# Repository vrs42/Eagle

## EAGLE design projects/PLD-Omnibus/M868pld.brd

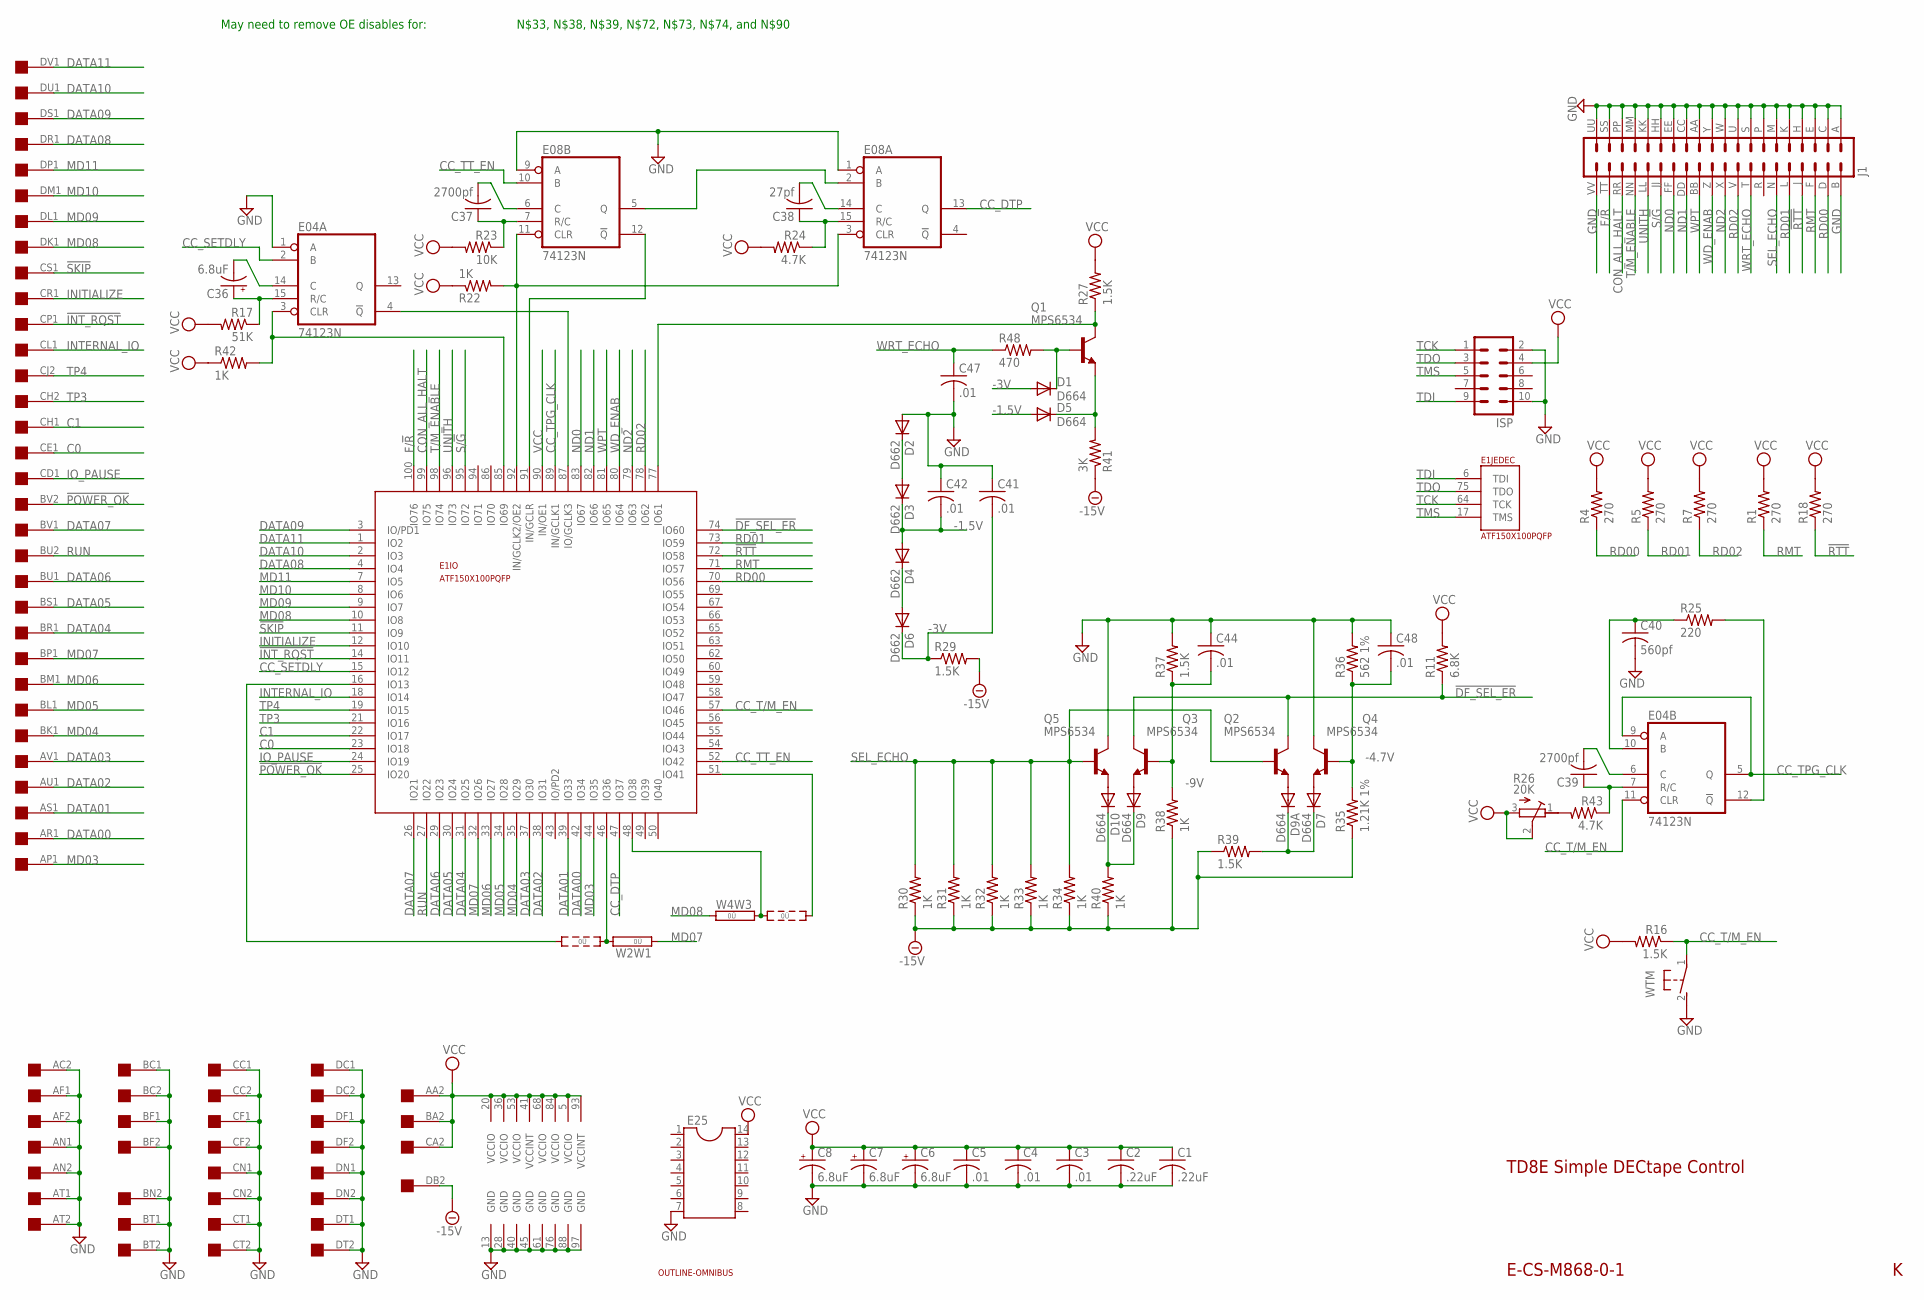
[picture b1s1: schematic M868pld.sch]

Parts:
C1, C2: .22uF; C050-025X075
C3, C4, C5, C41, C42, C44, C47, C48: .01; C050-025X075
C6, C7, C8, C36: 6.8uF; E12-8
C37, C39: 2700pf; C102-043X133
C38: 27pf; C050-025X075
C40: 560pf; C075-032X103
D1, D5, D7, D9, D9A, D10: D664; DO35-10
D2, D3, D4, D6: D662; DO35-10
E1: ATF150X100PQFP; PQFP-100
E04, E08: 74123N; DIL16
E25: DIL14
EDGE$3: QUAD; EDGE-CON8
ISP: MA05-2
J1: DEC40PINH
Q1, Q2, Q3, Q4, Q5: MPS6534; TO5
R1, R4, R5, R7, R18: 270; 0207/10
R11: 6.8K; 0207/10
R16, R27, R29, R37, R39: 1.5K; 0207/10
R17: 51K; 0207/10
R22, R30, R31, R32, R33, R34, R38, R40, R42: 1K; 0207/10
R23: 10K; 0207/10
R24, R43: 4.7K; 0207/10
R25: 220; 0207/10
R26: 20K; 3006Y
R35: 1.21K 1%; 0207/15
R36: 562 1%; 0207/15
R41: 3K; 0207/10
R48: 470; 0207/10
U$1: OUTLINE-OMNIBUS; OMNIBUS
W2W1, W4W3: 0R2; 0R2/10
WTM: 31-XX; B3F-31XX

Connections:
!CC_TPG_CLK: C40.1, E04.10 (B), R25.1
!DF_SEL_ER: E1.74 (IO60), Q2.3 (C), Q3.3 (C), R11.1
!INT_RQST: E1.14 (IO11), EDGE$3.CP1
!POWER_OK: E1.25 (IO20), EDGE$3.BV2
!RTT: E1.72 (IO58), J1.J (8), R18.1
!SKIP: E1.11 (IO9), EDGE$3.CS1
-1.5V: C42.2, D3.C, D4.A, D5.A
-3V: C41.2, D1.A, D6.C, R29.1
-4.7V: C48.2, Q4.2 (B), R35.2, R36.1
-9V: C44.2, Q3.2 (B), R37.1, R38.2
-15V: EDGE$3.DB2, R29.2, R30.1, R31.1, R32.1, R33.1, R34.1, R35.1, R38.1, R39.1, R40.1, R41.1
C0: E1.23 (IO18), EDGE$3.CE1
C1: E1.22 (IO17), EDGE$3.CH1
CC_DTP: E1.47 (IO37), E08.13 (Q)
CC_SETDLY: E1.15 (IO12), E04.2 (B)
CC_T/M_EN: E1.57 (IO46), E04.11 (CLR), R16.1, WTM.1
CC_TPG_CLK: E1.89 (IN/GCLK1), E04.5 (Q), E04.9 (A)
CC_TT_EN: E1.52 (IO42), E08.10 (B)
CON_ALL_HALT: E1.99 (IO75), J1.RR (36)
DATA00: E1.42 (IO34), EDGE$3.AR1
DATA01: E1.39 (IO33), EDGE$3.AS1
DATA02: E1.38 (IO31), EDGE$3.AU1
DATA03: E1.37 (IO30), EDGE$3.AV1
DATA04: E1.31 (IO25), EDGE$3.BR1
DATA05: E1.30 (IO24), EDGE$3.BS1
DATA06: E1.29 (IO23), EDGE$3.BU1
DATA07: E1.26 (IO21), EDGE$3.BV1
DATA08: E1.4 (IO4), EDGE$3.DR1
DATA09: E1.3 (IO/PD1), EDGE$3.DS1
DATA10: E1.2 (IO3), EDGE$3.DU1
DATA11: E1.1 (IO2), EDGE$3.DV1
F/!R: E1.100 (IO76), J1.TT (38)
GND: C1.2, C2.2, C3.2, C4.2, C5.2, C6.-, C7.-, C8.-, C40.2, C41.1, C42.1, C44.1, C47.2, C48.1, D2.A, E1.13 (GND), E1.28 (GND), E1.40 (GND), E1.45 (GND), E1.61 (GND), E1.76 (GND), E1.88 (GND), E1.97 (GND), E04.1 (A), E04.8 (GND), E08.1 (A), E08.8 (GND), E08.9 (A), E25.7, EDGE$3.AC2, EDGE$3.AF1, EDGE$3.AF2, EDGE$3.AN1, EDGE$3.AN2, EDGE$3.AT1, EDGE$3.AT2, EDGE$3.BC1, EDGE$3.BC2, EDGE$3.BF1, EDGE$3.BF2, EDGE$3.BN2, EDGE$3.BT1, EDGE$3.BT2, EDGE$3.CC1, EDGE$3.CC2, EDGE$3.CF1, EDGE$3.CF2, EDGE$3.CN1, EDGE$3.CN2, EDGE$3.CT1, EDGE$3.CT2, EDGE$3.DC1, EDGE$3.DC2, EDGE$3.DF1, EDGE$3.DF2, EDGE$3.DN1, EDGE$3.DN2, EDGE$3.DT1, EDGE$3.DT2, ISP.2, ISP.10, J1.A (1), J1.AA (23), J1.B (2), J1.C (3), J1.CC (25), J1.E (5), J1.EE (27), J1.H (7), J1.HH (29), J1.K (9), J1.KK (31), J1.M (11), J1.MM (33), J1.P (13), J1.PP (35), J1.S (15), J1.SS (37), J1.U (17), J1.UU (39), J1.VV (40), J1.W (19), J1.Y (21), Q4.3 (C), Q5.3 (C), R36.2, R37.2, WTM.2 (S)
INITIALIZE: E1.12 (IO10), EDGE$3.CR1
INTERNAL_IO: E1.18 (IO14), EDGE$3.CL1
IO_PAUSE: E1.24 (IO19), EDGE$3.CD1
MD03: E1.44 (IO35), EDGE$3.AP1
MD04: E1.35 (IO29), EDGE$3.BK1
MD05: E1.34 (IO28), EDGE$3.BL1
MD06: E1.33 (IO27), EDGE$3.BM1
MD07: E1.32 (IO26), EDGE$3.BP1, W2W1.1
MD08: E1.10 (IO8), EDGE$3.DK1, W4W3.1
MD09: E1.9 (IO7), EDGE$3.DL1
MD10: E1.8 (IO6), EDGE$3.DM1
MD11: E1.7 (IO5), EDGE$3.DP1
unnamed: E1.92 (IN/GCLK2/OE2), E08.3 (CLR), E08.11 (CLR), R22.2
unnamed: D1.C, Q1.2 (B), R48.2
unnamed: D5.C, Q1.1 (E), R41.2
unnamed: E1.77 (IO61), Q1.3 (C), R27.1
unnamed: D2.C, D3.A
unnamed: D9.C, D10.C, R40.2
unnamed: D4.C, D6.A
unnamed: D10.A, Q5.1 (E)
unnamed: D9.A, Q3.1 (E)
unnamed: D9A.A, Q2.1 (E)
unnamed: D7.A, Q4.1 (E)
unnamed: E1.46 (IO36), W2W1.2
unnamed: E1.48 (IO38), W4W3.2
unnamed: D7.C, D9A.C, R39.2
unnamed: E1.16 (IO13), W2W1.3
unnamed: E1.51 (IO41), W4W3.3
unnamed: E08.2 (B), E08.5 (Q)
unnamed: C37.1, E08.7 (R/C), R23.1
unnamed: C38.1, E08.15 (R/C), R24.1
unnamed: E1.91 (IN/GCLR), E08.12 (!Q)
unnamed: C38.2, E08.14 (C)
unnamed: C37.2, E08.6 (C)
unnamed: E1.85 (IO69), E04.3 (CLR), R42.2
unnamed: C36.+, E04.15 (R/C), R17.1
unnamed: C36.-, E04.14 (C)
unnamed: E1.87 (IO/GCLK3), E04.4 (!Q)
unnamed: C39.1, E04.7 (R/C), R43.1
unnamed: C39.2, E04.6 (C)
unnamed: R26.1 (A), R43.2
unnamed: E04.12 (!Q), R25.2
ND0: E1.83 (IO67), J1.FF (28)
ND1: E1.82 (IO66), J1.DD (26)
ND2: E1.79 (IO63), J1.X (20)
RD00: E1.70 (IO56), J1.D (4), R4.1
RD01: E1.73 (IO59), J1.L (10), R5.1
RD02: E1.78 (IO62), J1.V (18), R7.1
RMT: E1.71 (IO57), J1.F (6), R1.1
RUN: E1.27 (IO22), EDGE$3.BU2
S/!G: E1.95 (IO72), J1.JJ (30)
SEL_ECHO: J1.N (12), Q2.2 (B), Q5.2 (B), R30.2, R31.2, R32.2, R33.2, R34.2
T/M_ENABLE: E1.98 (IO74), J1.NN (34)
TCK: E1.64 (TCK), ISP.1
TDI: E1.6 (TDI), ISP.9
TDO: E1.75 (TDO), ISP.3
TMS: E1.17 (TMS), ISP.5
TP3: E1.21 (IO16), EDGE$3.CH2
TP4: E1.19 (IO15), EDGE$3.CJ2
UNITH: E1.96 (IO73), J1.LL (32)
VCC: C1.1, C2.1, C3.1, C4.1, C5.1, C6.+, C7.+, C8.+, E1.5 (VCCIO), E1.20 (VCCIO), E1.36 (VCCIO), E1.41 (VCCINT), E1.53 (VCCIO), E1.68 (VCCIO), E1.84 (VCCIO), E1.90 (IN/OE1), E1.93 (VCCINT), E04.16 (VCC), E08.16 (VCC), E25.14, EDGE$3.AA2, EDGE$3.BA2, EDGE$3.CA2, ISP.4, R1.2, R4.2, R5.2, R7.2, R11.2, R16.2, R17.2, R18.2, R22.1, R23.2, R24.2, R26.2 (S), R26.3 (E), R27.2, R42.1
WD_ENAB: E1.80 (IO64), J1.Z (22)
WPT: E1.81 (IO65), J1.BB (24)
WRT_ECHO: C47.1, J1.T (16), R48.1

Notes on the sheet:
E-CS-M868-0-1
TD8E Simple DECtape Control
May need to remove OE disables for:
N$33, N$38, N$39, N$72, N$73, N$74, and N$90

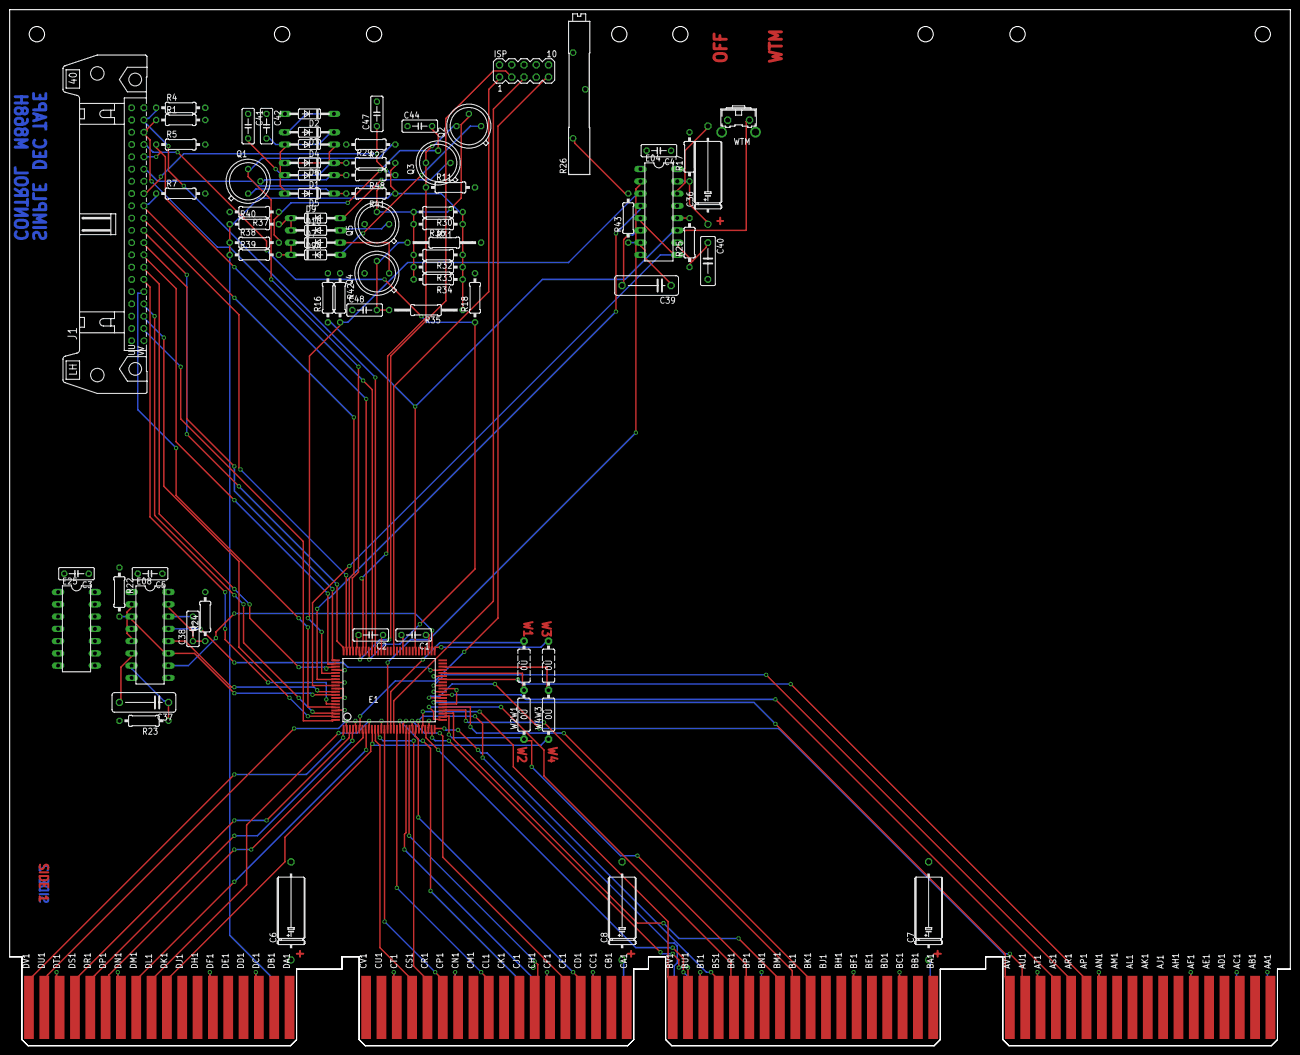
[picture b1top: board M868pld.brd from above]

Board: 4 copper layers, 265.3 x 214.6 mm, 74 parts (0 on the bottom side), 97 nets.

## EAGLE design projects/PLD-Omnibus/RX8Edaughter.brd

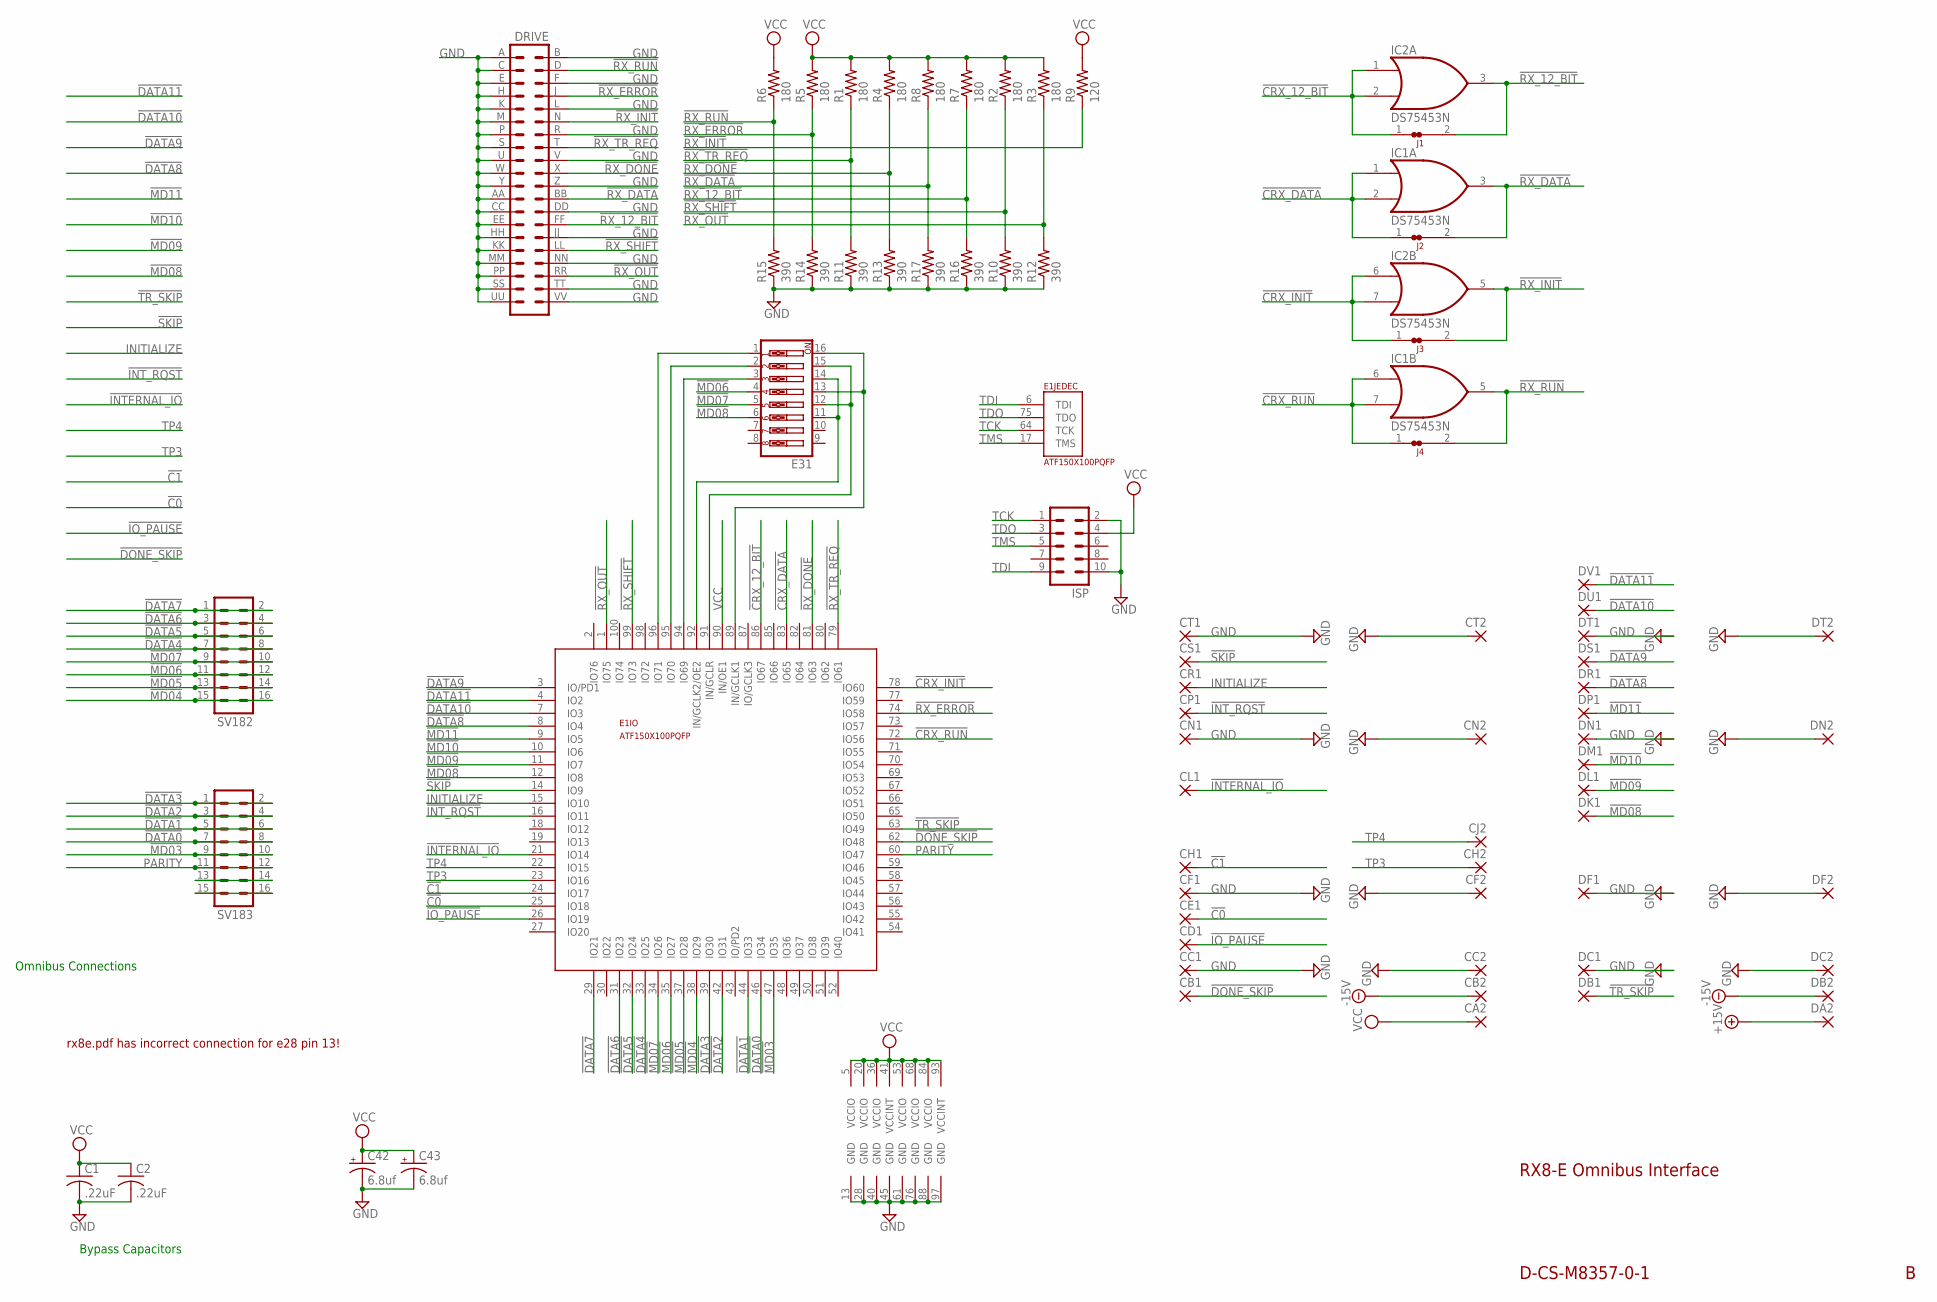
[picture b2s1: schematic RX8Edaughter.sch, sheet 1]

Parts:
C1, C2: .22uF; C050-025X075
C42, C43: 6.8uf; E22-6
CA2: 1,6/0,9
CB1, CB2: 1,6/0,9
CC1, CC2: 1,6/0,9
CD1: 1,6/0,9
CE1: 1,6/0,9
CF1, CF2: 1,6/0,9
CH1, CH2: 1,6/0,9
CJ2: 1,6/0,9
CL1: 1,6/0,9
CN1, CN2: 1,6/0,9
CP1: 1,6/0,9
CR1: 1,6/0,9
CS1: 1,6/0,9
CT1, CT2: 1,6/0,9
DA2: 1,6/0,9
DB1, DB2: 1,6/0,9
DC1, DC2: 1,6/0,9
DF1, DF2: 1,6/0,9
DK1: 1,6/0,9
DL1: 1,6/0,9
DM1: 1,6/0,9
DN1, DN2: 1,6/0,9
DP1: 1,6/0,9
DR1: 1,6/0,9
DRIVE: DEC40PINH
DS1: 1,6/0,9
DT1, DT2: 1,6/0,9
DU1: 1,6/0,9
DV1: 1,6/0,9
E1: ATF150X100PQFP; PQFP-100
E31: SW_DIP-8; EDG-08
IC1, IC2: DS75453N; DIL08
ISP: ML10
J1, J2, J3, J4: JUMPER-NC2; NC2
R1, R2, R3, R4, R5, R6, R7, R8: 180; 0207/10
R9: 120; 0207/10
R10, R11, R12, R13, R14, R15, R16, R17: 390; 0207/10
SV182, SV183: MA08-2

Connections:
!C0: CE1.1, E1.25 (IO18)
!C1: CH1.1, E1.24 (IO17)
!CRX_12_BIT: E1.86 (IO67), IC2.1 (I0), IC2.2 (I1), J1.1
!CRX_DATA: E1.83 (IO65), IC1.1 (I0), IC1.2 (I1), J2.1
!CRX_INIT: E1.78 (IO60), IC2.6 (I0), IC2.7 (I1), J3.1
!CRX_RUN: E1.72 (IO56), IC1.6 (I0), IC1.7 (I1), J4.1
!DATA0: E1.46 (IO34), SV183.7, SV183.8
!DATA1: E1.44 (IO33), SV183.5, SV183.6
!DATA2: E1.42 (IO31), SV183.3, SV183.4
!DATA3: E1.39 (IO30), SV183.1, SV183.2
!DATA4: E1.33 (IO25), SV182.7, SV182.8
!DATA5: E1.32 (IO24), SV182.5, SV182.6
!DATA6: E1.31 (IO23), SV182.3, SV182.4
!DATA7: E1.29 (IO21), SV182.1, SV182.2
!DATA8: DR1.1, E1.8 (IO4)
!DATA9: DS1.1, E1.3 (IO/PD1)
!DATA10: DU1.1, E1.7 (IO3)
!DATA11: DV1.1, E1.4 (IO2)
!DONE_SKIP: CB1.1, E1.62 (IO48)
!INTERNAL_IO: CL1.1, E1.21 (IO14)
!INT_RQST: CP1.1, E1.16 (IO11)
!IO_PAUSE: CD1.1, E1.26 (IO19)
!MD03: E1.47 (IO35), SV183.9, SV183.10
!MD04: E1.38 (IO29), SV182.15, SV182.16
!MD05: E1.37 (IO28), SV182.13, SV182.14
!MD06: E1.35 (IO27), E31.4, SV182.11, SV182.12
!MD07: E1.34 (IO26), E31.5, SV182.9, SV182.10
!MD08: DK1.1, E1.12 (IO8), E31.6
!MD09: DL1.1, E1.11 (IO7)
!MD10: DM1.1, E1.10 (IO6)
!MD11: DP1.1, E1.9 (IO5)
!RX_12_BIT: DRIVE.FF (28), IC2.3 (O), J1.2, R7.1, R16.2
!RX_DATA: DRIVE.BB (24), IC1.3 (O), J2.2, R8.1, R17.2
!RX_DONE: DRIVE.X (20), E1.81 (IO63), R4.1, R13.2
!RX_ERROR: DRIVE.J (8), E1.74 (IO58), R5.1, R14.2
!RX_INIT: DRIVE.N (12), IC2.5 (O), J3.2, R9.1
!RX_OUT: DRIVE.RR (36), E1.1 (IO75), R3.1, R12.2
!RX_RUN: DRIVE.D (4), IC1.5 (O), J4.2, R6.1, R15.2
!RX_SHIFT: DRIVE.LL (32), E1.99 (IO73), R2.1, R10.2
!RX_TR_REQ: DRIVE.T (16), E1.79 (IO61), R1.1, R11.2
!SKIP: CS1.1, E1.14 (IO9)
!TR_SKIP: DB1.1, E1.63 (IO49)
+15V: DA2.1
-15V: CB2.1, DB2.1
GND: C1.2, C2.2, C42.-, C43.-, CC1.1, CC2.1, CF1.1, CF2.1, CN1.1, CN2.1, CT1.1, CT2.1, DC1.1, DC2.1, DF1.1, DF2.1, DN1.1, DN2.1, DRIVE.A (1), DRIVE.AA (23), DRIVE.B (2), DRIVE.C (3), DRIVE.CC (25), DRIVE.DD (26), DRIVE.E (5), DRIVE.EE (27), DRIVE.F (6), DRIVE.H (7), DRIVE.HH (29), DRIVE.JJ (30), DRIVE.K (9), DRIVE.KK (31), DRIVE.L (10), DRIVE.M (11), DRIVE.MM (33), DRIVE.NN (34), DRIVE.P (13), DRIVE.PP (35), DRIVE.R (14), DRIVE.S (15), DRIVE.SS (37), DRIVE.TT (38), DRIVE.U (17), DRIVE.UU (39), DRIVE.V (18), DRIVE.VV (40), DRIVE.W (19), DRIVE.Y (21), DRIVE.Z (22), DT1.1, DT2.1, E1.13 (GND), E1.28 (GND), E1.40 (GND), E1.45 (GND), E1.61 (GND), E1.76 (GND), E1.88 (GND), E1.97 (GND), IC1.4 (GND), IC2.4 (GND), ISP.2, ISP.10, R10.1, R11.1, R12.1, R13.1, R14.1, R15.1, R16.1, R17.1; also elsewhere on the board
INITIALIZE: CR1.1, E1.15 (IO10)
unnamed: E1.94 (IO69), E31.3
unnamed: E1.95 (IO70), E31.2
unnamed: E1.96 (IO71), E31.1
unnamed: E1.92 (IN/GCLK2/OE2), E31.11, E31.14
unnamed: E1.91 (IN/GCLR), E31.12, E31.15
unnamed: E1.89 (IN/GCLK1), E31.13, E31.16
unnamed: SV183.13, SV183.14
unnamed: SV183.15, SV183.16
PARITY: E1.60 (IO47), SV183.11, SV183.12
TCK: E1.64 (TCK), ISP.1
TDI: E1.6 (TDI), ISP.9
TDO: E1.75 (TDO), ISP.3
TMS: E1.17 (TMS), ISP.5
TP3: CH2.1, E1.23 (IO16)
TP4: CJ2.1, E1.22 (IO15)
VCC: C1.1, C2.1, C42.+, C43.+, CA2.1, E1.5 (VCCIO), E1.20 (VCCIO), E1.36 (VCCIO), E1.41 (VCCINT), E1.53 (VCCIO), E1.68 (VCCIO), E1.84 (VCCIO), E1.90 (IN/OE1), E1.93 (VCCINT), IC1.8 (VCC), IC2.8 (VCC), ISP.4, R1.2, R2.2, R3.2, R4.2, R5.2, R6.2, R7.2, R8.2, R9.2; also elsewhere on the board

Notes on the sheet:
rx8e.pdf has incorrect connection for e28 pin 13!
Omnibus Connections
Bypass Capacitors
D-CS-M8357-0-1
RX8-E Omnibus Interface

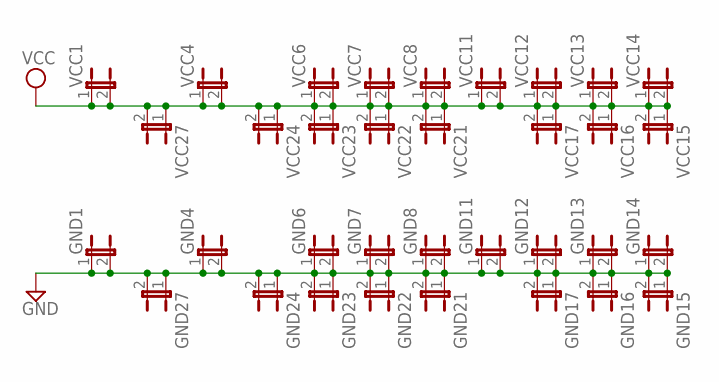
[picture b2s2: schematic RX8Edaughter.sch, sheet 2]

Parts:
GND1, GND4, GND6, GND7, GND8, GND11, GND12, GND13, GND14, GND15, GND16, GND17, GND21, GND22, GND23, GND24, GND27: JP1E; JP1
VCC1, VCC4, VCC6, VCC7, VCC8, VCC11, VCC12, VCC13, VCC14, VCC15, VCC16, VCC17, VCC21, VCC22, VCC23, VCC24, VCC27: JP1E; JP1

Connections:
GND: GND1.1, GND1.2, GND4.1, GND4.2, GND6.1, GND6.2, GND7.1, GND7.2, GND8.1, GND8.2, GND11.1, GND11.2, GND12.1, GND12.2, GND13.1, GND13.2, GND14.1, GND14.2, GND15.1, GND15.2, GND16.1, GND16.2, GND17.1, GND17.2, GND21.1, GND21.2, GND22.1, GND22.2, GND23.1, GND23.2, GND24.1, GND24.2, GND27.1, GND27.2; also elsewhere on the board
VCC: VCC1.1, VCC1.2, VCC4.1, VCC4.2, VCC6.1, VCC6.2, VCC7.1, VCC7.2, VCC8.1, VCC8.2, VCC11.1, VCC11.2, VCC12.1, VCC12.2, VCC13.1, VCC13.2, VCC14.1, VCC14.2, VCC15.1, VCC15.2, VCC16.1, VCC16.2, VCC17.1, VCC17.2, VCC21.1, VCC21.2, VCC22.1, VCC22.2, VCC23.1, VCC23.2, VCC24.1, VCC24.2, VCC27.1, VCC27.2; also elsewhere on the board

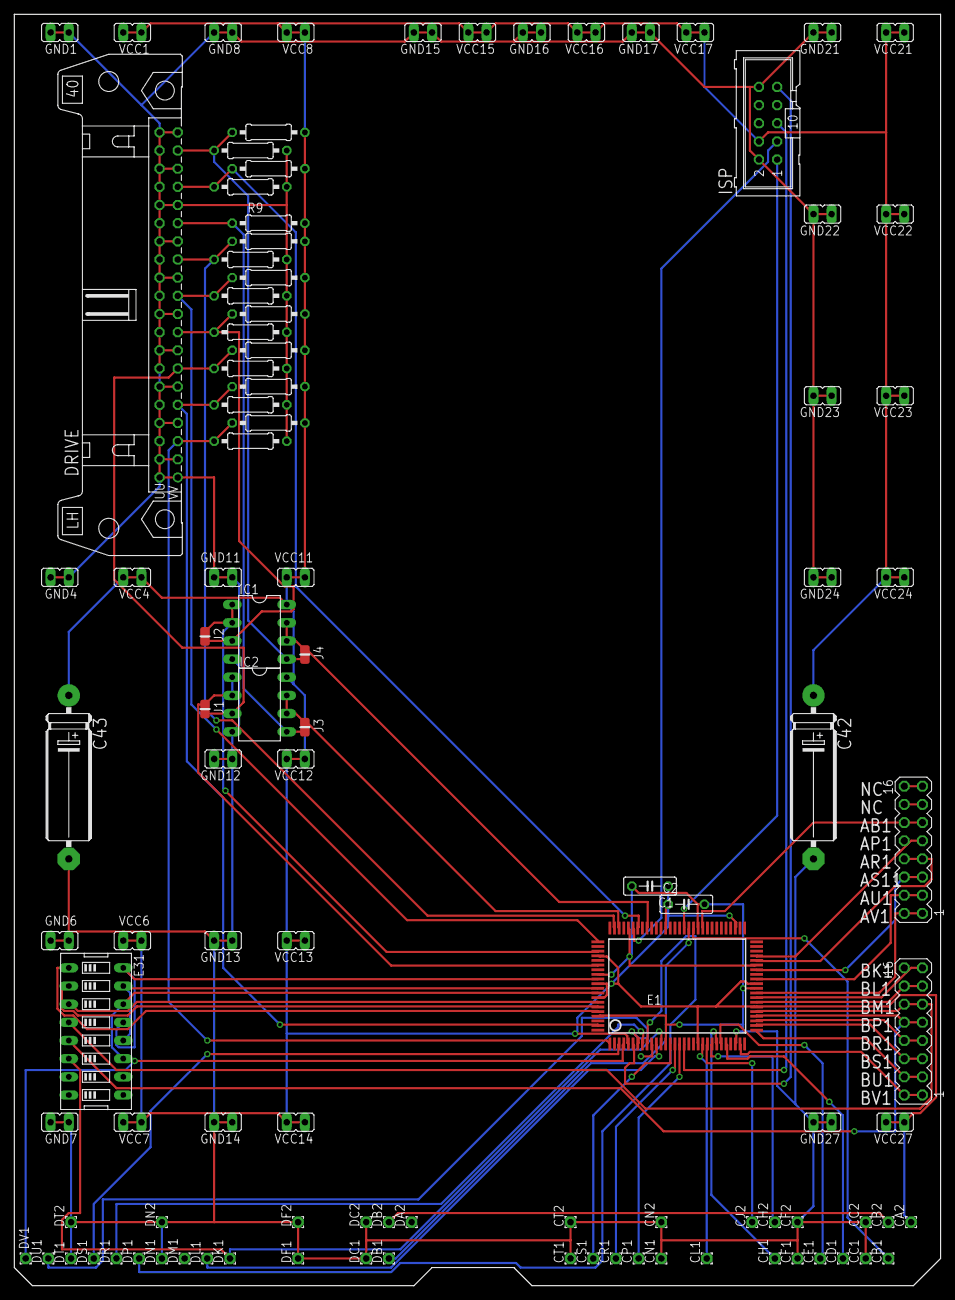
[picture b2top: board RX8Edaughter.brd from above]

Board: 4 copper layers, 129.5 x 177.8 mm, 106 parts (0 on the bottom side), 61 nets.

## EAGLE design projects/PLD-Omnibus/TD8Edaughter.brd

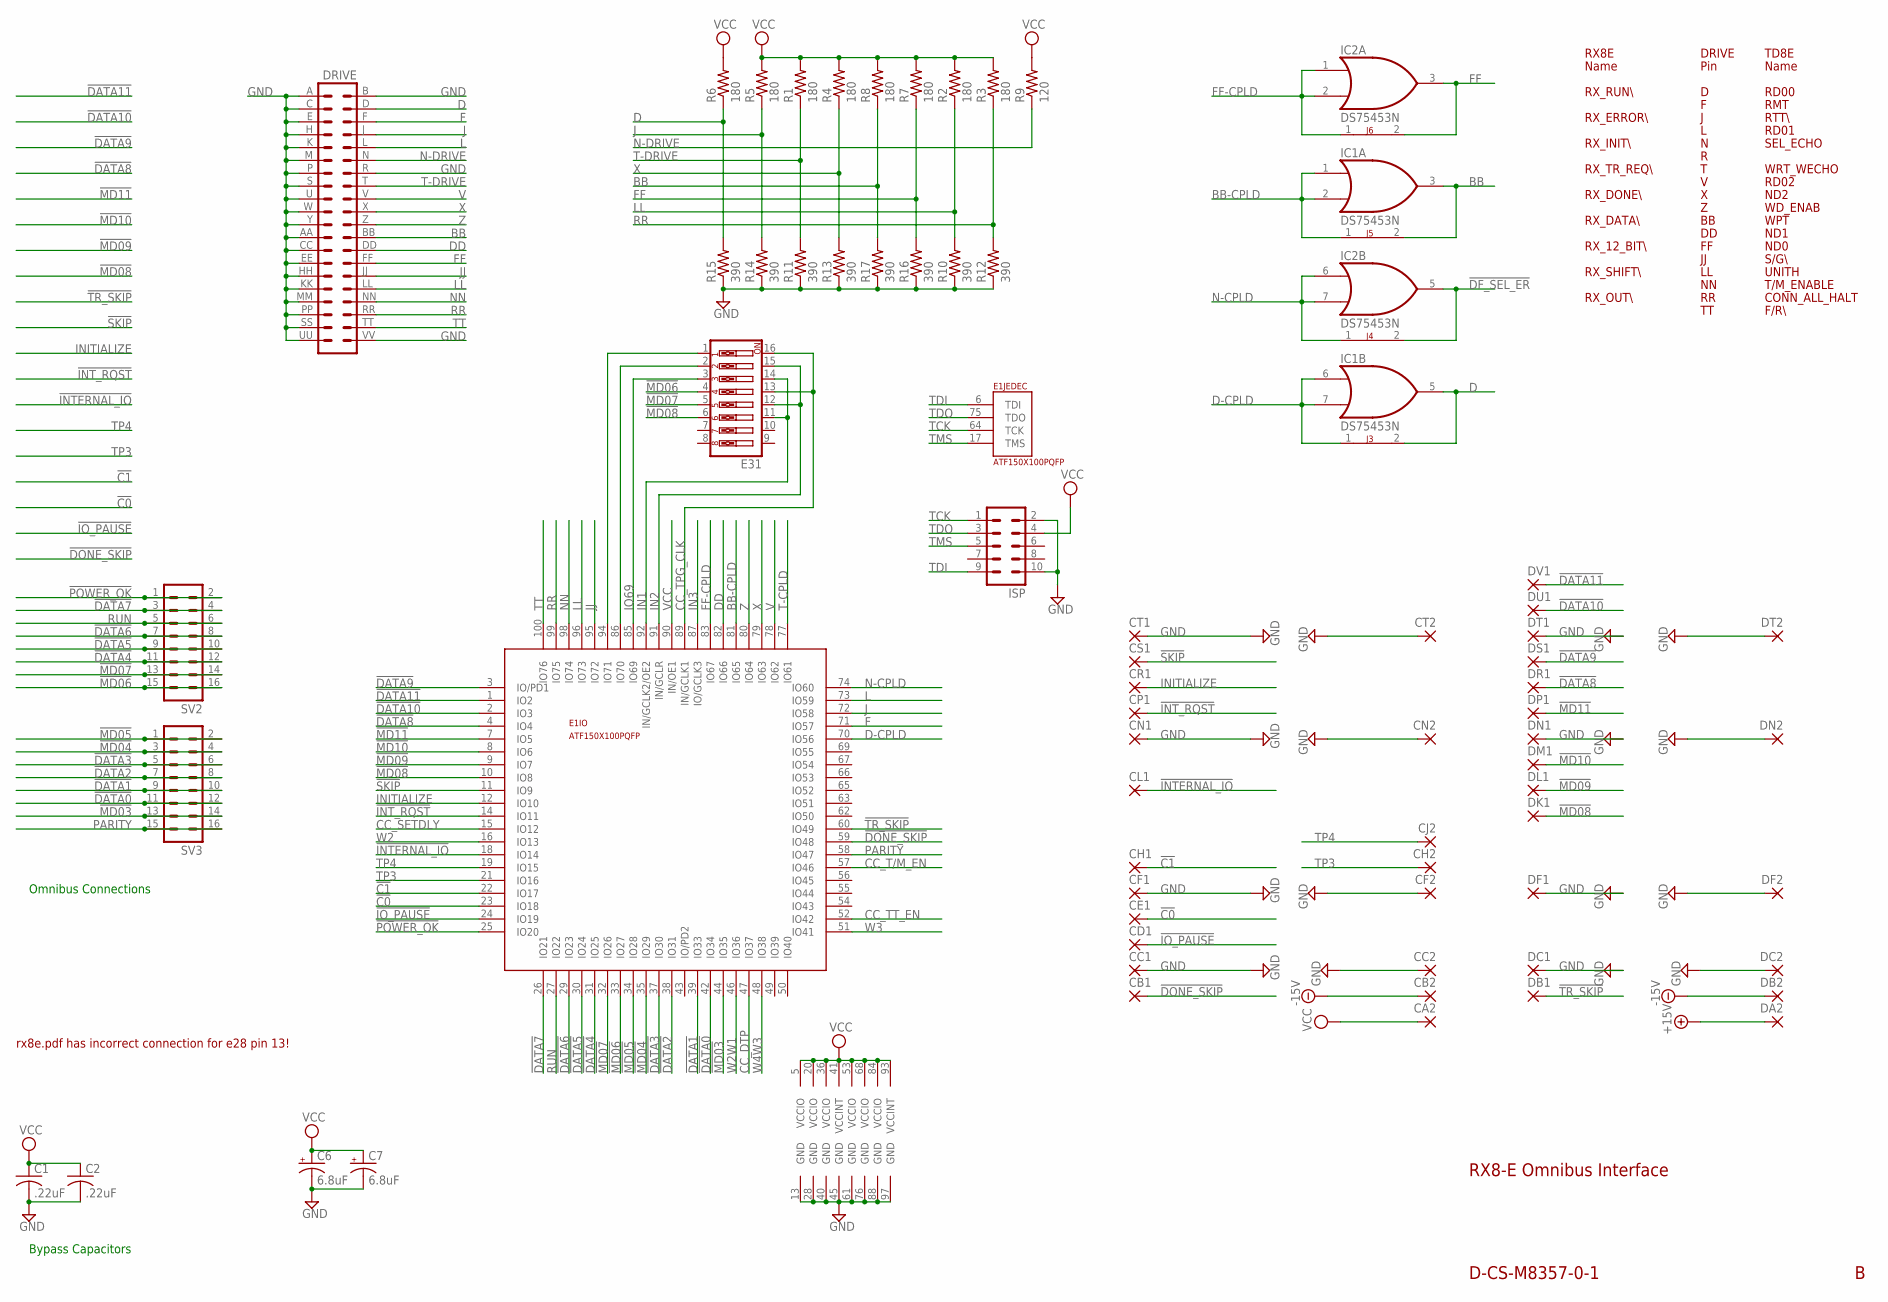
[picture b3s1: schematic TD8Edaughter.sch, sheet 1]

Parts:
C1, C2: .22uF; C050-025X075
C6, C7: 6.8uF; E12-8
CA2: 1,6/0,9
CB1, CB2: 1,6/0,9
CC1, CC2: 1,6/0,9
CD1: 1,6/0,9
CE1: 1,6/0,9
CF1, CF2: 1,6/0,9
CH1, CH2: 1,6/0,9
CJ2: 1,6/0,9
CL1: 1,6/0,9
CN1, CN2: 1,6/0,9
CP1: 1,6/0,9
CR1: 1,6/0,9
CS1: 1,6/0,9
CT1, CT2: 1,6/0,9
DA2: 1,6/0,9
DB1, DB2: 1,6/0,9
DC1, DC2: 1,6/0,9
DF1, DF2: 1,6/0,9
DK1: 1,6/0,9
DL1: 1,6/0,9
DM1: 1,6/0,9
DN1, DN2: 1,6/0,9
DP1: 1,6/0,9
DR1: 1,6/0,9
DRIVE: DEC40PINH
DS1: 1,6/0,9
DT1, DT2: 1,6/0,9
DU1: 1,6/0,9
DV1: 1,6/0,9
E1: ATF150X100PQFP; PQFP-100
E31: SW_DIP-8; EDG-08
IC1, IC2: DS75453N; DIL08
ISP: ML10
J3, J4, J5, J6: JUMPER-NC2; NC2
R1, R2, R3, R4, R5, R6, R7, R8: 180; 0207/10
R9: 120; 0207/10
R10, R11, R12, R13, R14, R15, R16, R17: 390; 0207/10
SV2, SV3: MA08-2

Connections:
!C0: CE1.1, E1.23 (IO18)
!C1: CH1.1, E1.22 (IO17)
!DATA0: E1.42 (IO34), SV3.11, SV3.12
!DATA1: E1.39 (IO33), SV3.9, SV3.10
!DATA2: E1.38 (IO31), SV3.7, SV3.8
!DATA3: E1.37 (IO30), SV3.5, SV3.6
!DATA4: E1.31 (IO25), SV2.11, SV2.12
!DATA5: E1.30 (IO24), SV2.9, SV2.10
!DATA6: E1.29 (IO23), SV2.7, SV2.8
!DATA7: E1.26 (IO21), SV2.3, SV2.4
!DATA8: DR1.1, E1.4 (IO4)
!DATA9: DS1.1, E1.3 (IO/PD1)
!DATA10: DU1.1, E1.2 (IO3)
!DATA11: DV1.1, E1.1 (IO2)
!DF_SEL_ER: IC2.5 (O), J4.2; also elsewhere on the board
!DONE_SKIP: CB1.1, E1.59 (IO48)
!INTERNAL_IO: CL1.1, E1.18 (IO14)
!INT_RQST: CP1.1, E1.14 (IO11)
!IO_PAUSE: CD1.1, E1.24 (IO19)
!MD03: E1.44 (IO35), SV3.13, SV3.14
!MD04: E1.35 (IO29), SV3.3, SV3.4
!MD05: E1.34 (IO28), SV3.1, SV3.2
!MD06: E1.33 (IO27), E31.4, SV2.15, SV2.16
!MD07: E1.32 (IO26), E31.5, SV2.13, SV2.14; also elsewhere on the board
!MD08: DK1.1, E1.10 (IO8), E31.6; also elsewhere on the board
!MD09: DL1.1, E1.9 (IO7)
!MD10: DM1.1, E1.8 (IO6)
!MD11: DP1.1, E1.7 (IO5)
!POWER_OK: E1.25 (IO20), SV2.1, SV2.2
!SKIP: CS1.1, E1.11 (IO9)
!TR_SKIP: DB1.1, E1.60 (IO49)
+15V: DA2.1
-15V: CB2.1, DB2.1; also elsewhere on the board
BB: DRIVE.BB (24), IC1.3 (O), J5.2, R8.1, R17.2
BB-CPLD: E1.81 (IO65), IC1.1 (I0), IC1.2 (I1), J5.1
CC_DTP: E1.47 (IO37); also elsewhere on the board
CC_SETDLY: E1.15 (IO12); also elsewhere on the board
CC_T/M_EN: E1.57 (IO46); also elsewhere on the board
CC_TPG_CLK: E1.89 (IN/GCLK1), E31.13, E31.16; also elsewhere on the board
CC_TT_EN: E1.52 (IO42); also elsewhere on the board
D: DRIVE.D (4), IC1.5 (O), J3.2, R6.1, R15.2; also elsewhere on the board
D-CPLD: E1.70 (IO56), IC1.6 (I0), IC1.7 (I1), J3.1
DD: DRIVE.DD (26), E1.82 (IO66)
F: DRIVE.F (6), E1.71 (IO57); also elsewhere on the board
FF: DRIVE.FF (28), IC2.3 (O), J6.2, R7.1, R16.2
FF-CPLD: E1.83 (IO67), IC2.1 (I0), IC2.2 (I1), J6.1
GND: C1.2, C2.2, C6.-, C7.-, CC1.1, CC2.1, CF1.1, CF2.1, CN1.1, CN2.1, CT1.1, CT2.1, DC1.1, DC2.1, DF1.1, DF2.1, DN1.1, DN2.1, DRIVE.A (1), DRIVE.AA (23), DRIVE.B (2), DRIVE.C (3), DRIVE.CC (25), DRIVE.E (5), DRIVE.EE (27), DRIVE.H (7), DRIVE.HH (29), DRIVE.K (9), DRIVE.KK (31), DRIVE.M (11), DRIVE.MM (33), DRIVE.P (13), DRIVE.PP (35), DRIVE.R (14), DRIVE.S (15), DRIVE.SS (37), DRIVE.U (17), DRIVE.UU (39), DRIVE.VV (40), DRIVE.W (19), DRIVE.Y (21), DT1.1, DT2.1, E1.13 (GND), E1.28 (GND), E1.40 (GND), E1.45 (GND), E1.61 (GND), E1.76 (GND), E1.88 (GND), E1.97 (GND), IC1.4 (GND), IC2.4 (GND), ISP.2, ISP.10, R10.1, R11.1, R12.1, R13.1, R14.1, R15.1, R16.1, R17.1; also elsewhere on the board
IN1: E1.92 (IN/GCLK2/OE2), E31.11, E31.14; also elsewhere on the board
IN2: E1.91 (IN/GCLR), E31.12, E31.15; also elsewhere on the board
IN3: E1.87 (IO/GCLK3); also elsewhere on the board
INITIALIZE: CR1.1, E1.12 (IO10)
IO69: E1.85 (IO69), E31.3; also elsewhere on the board
J: DRIVE.J (8), E1.72 (IO58), R5.1, R14.2; also elsewhere on the board
JJ: DRIVE.JJ (30), E1.95 (IO72)
L: DRIVE.L (10), E1.73 (IO59); also elsewhere on the board
LL: DRIVE.LL (32), E1.96 (IO73), R2.1, R10.2
unnamed: E1.86 (IO70), E31.2
unnamed: E1.94 (IO71), E31.1
N-CPLD: E1.74 (IO60), IC2.6 (I0), IC2.7 (I1), J4.1
N-DRIVE: DRIVE.N (12), R9.1; also elsewhere on the board
NN: DRIVE.NN (34), E1.98 (IO74)
PARITY: E1.58 (IO47), SV3.15, SV3.16
RR: DRIVE.RR (36), E1.99 (IO75), R3.1, R12.2
RUN: E1.27 (IO22), SV2.5, SV2.6
T-CPLD: E1.77 (IO61); also elsewhere on the board
T-DRIVE: DRIVE.T (16), R1.1, R11.2; also elsewhere on the board
TCK: E1.64 (TCK), ISP.1
TDI: E1.6 (TDI), ISP.9
TDO: E1.75 (TDO), ISP.3
TMS: E1.17 (TMS), ISP.5
TP3: CH2.1, E1.21 (IO16)
TP4: CJ2.1, E1.19 (IO15)
TT: DRIVE.TT (38), E1.100 (IO76)
V: DRIVE.V (18), E1.78 (IO62); also elsewhere on the board
VCC: C1.1, C2.1, C6.+, C7.+, CA2.1, E1.5 (VCCIO), E1.20 (VCCIO), E1.36 (VCCIO), E1.41 (VCCINT), E1.53 (VCCIO), E1.68 (VCCIO), E1.84 (VCCIO), E1.90 (IN/OE1), E1.93 (VCCINT), IC1.8 (VCC), IC2.8 (VCC), ISP.4, R1.2, R2.2, R3.2, R4.2, R5.2, R6.2, R7.2, R8.2, R9.2; also elsewhere on the board
W2: E1.16 (IO13); also elsewhere on the board
W2W1: E1.46 (IO36); also elsewhere on the board
W3: E1.51 (IO41); also elsewhere on the board
W4W3: E1.48 (IO38); also elsewhere on the board
X: DRIVE.X (20), E1.79 (IO63), R4.1, R13.2
Z: DRIVE.Z (22), E1.80 (IO64)

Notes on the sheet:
rx8e.pdf has incorrect connection for e28 pin 13!
Omnibus Connections
Bypass Capacitors
D-CS-M8357-0-1
RX8-E Omnibus Interface
DRIVE
Pin
RD00
RMT
RTT\\
RD01
SEL_ECHO
WRT_WECHO
RD02
ND2
WD_ENAB
WPT
ND1
ND0
S/G\\
UNITH
T/M_ENABLE
CONN_ALL_HALT
F/R\\
TD8E
Name
RX_RUN\\
RX_ERROR\\
RX_INIT\\
RX_TR_REQ\\
RX_DONE\\
RX_DATA\\
RX_12_BIT\\
RX_SHIFT\\
RX_OUT\\
RX8E
